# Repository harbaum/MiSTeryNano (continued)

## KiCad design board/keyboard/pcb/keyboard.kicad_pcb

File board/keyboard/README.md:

# MiSTeryNano - Mini ST keyboard

This is a work in progress. It's meant to become a half size keyboard
inspired by the Atari ST series. It's meant to become the basis
of some kind of Mini Atari ST based on the MiSTeryNano FPGA.

They keyboard is primarily designed to be a fully functional design
suited for simple use cases like renaming a file or selecting game
options. It's not meant to be usable to write texts or for any other
productive use case.

## Hardware

The [hardware](pcb) consists of cheap 7x7mm 6 pin momentary switches. These
switches are arranged in the same 15*8 matrix used inside the original
Atari ST keyboard.

The matrix is addressed via serial shift registers requiring four pins
on the controlling device. Two 8-bit serial to parallel shift
registers are used to drive the 15 columnns and a single serial to
parallel shift register is being used to read the eight rows. For
further info on reading the matrix via the serial interface refer
to the [kbd_test Arduino test sketch](kbd_test). The 16th output of
the serial shift registers drive a user conrollable LED in the top right
corner similarily placed to the floppy LED on a Atari STF. This might e.g.
be used in an emulation environment to indicate disk/sd card activity.

The keyboard can either be driven by 3.3V or by 5V and is thus compatible
with nearly all microcontrollers as well as many consumer FPGAs.

## Arduino sketches

The MiSTeryNano keyboard comes with two Arduino sketches. The
[kbd_test](kbd_test) sketch can be installed onto any regular Arduino
Uno, Nano or the Micro and permanently scans the keyboard for pressed
keys and reports the in plain text on the serial monitor. The sketch
also permanently flashes the user led in the top left corner of the
keyboard.  The [arduino_hid](arduino_hid) sketch is meant to be used
in a Sparkfun Pro Micro or Arduino Micro and presents the MiSTeryNano
keyboard as a regular USB keyboard to e.g. a PC or Raspberry Pi. This
sketch uses the user LED to indicate the Caps Lock state and emits F12
for the international key. The later is useful for the US keycaps as
the international key (right of the left shift key) is not present on
US keyboards and can this way be used to open the on-screen-display
or an emulator menu.

## Keycaps

The keycaps have been designed to be printable on a Bambulab Carbon X1
using a 0.4mm nozzle, 0.8mm layer height and two colors of PETG filament.

The keycaps are being designed in FreeCAD using a small macro script
to derive the various variants from a small set of designs. This also
exports [STL files](stl) for printing as well as [WRL files](wrl) for
rendering in kicad.

The image at the top shows they keyboard with US keycaps as currently
designed. The PCB supports the international key right to the left
shift key as well. In the US variant it's covered by the bigger keycap
of the left shift key.

## Assembly

Initially all SMD parts are mounted. The general function can then
be tested with the Arduino test sketch controlling the LED and reacting
to contacts being simulated using tweezers or the like.

Be careful about the orientation when mounting the switches. They will only work correctly in one of the possible two orientations. There are different variants, one e.g. having a bigger opening on the white cover tab or a dot painted on indicating the side to face the keyboards front. It's recommended to test a few switches without soldering them in to verify the correct orientation.

Some optional aligmment spacer grids can be used to help align the
switches during assembly.

All switches and keys are then plugged into these
spacers.

All keypad switches are in place.

The remaining keys are installed and tested row by row.

Finally the keyboard is complete.

A sparkfun Arduino Pro Micro allows the keyboard to
act as a real USB HID keyboard to be used with any PC
or Raspberry Pi or even the FPGA Compantion.

See [this video](https://youtube.com/shorts/clQujxjdr9I) for some
real life typing action.

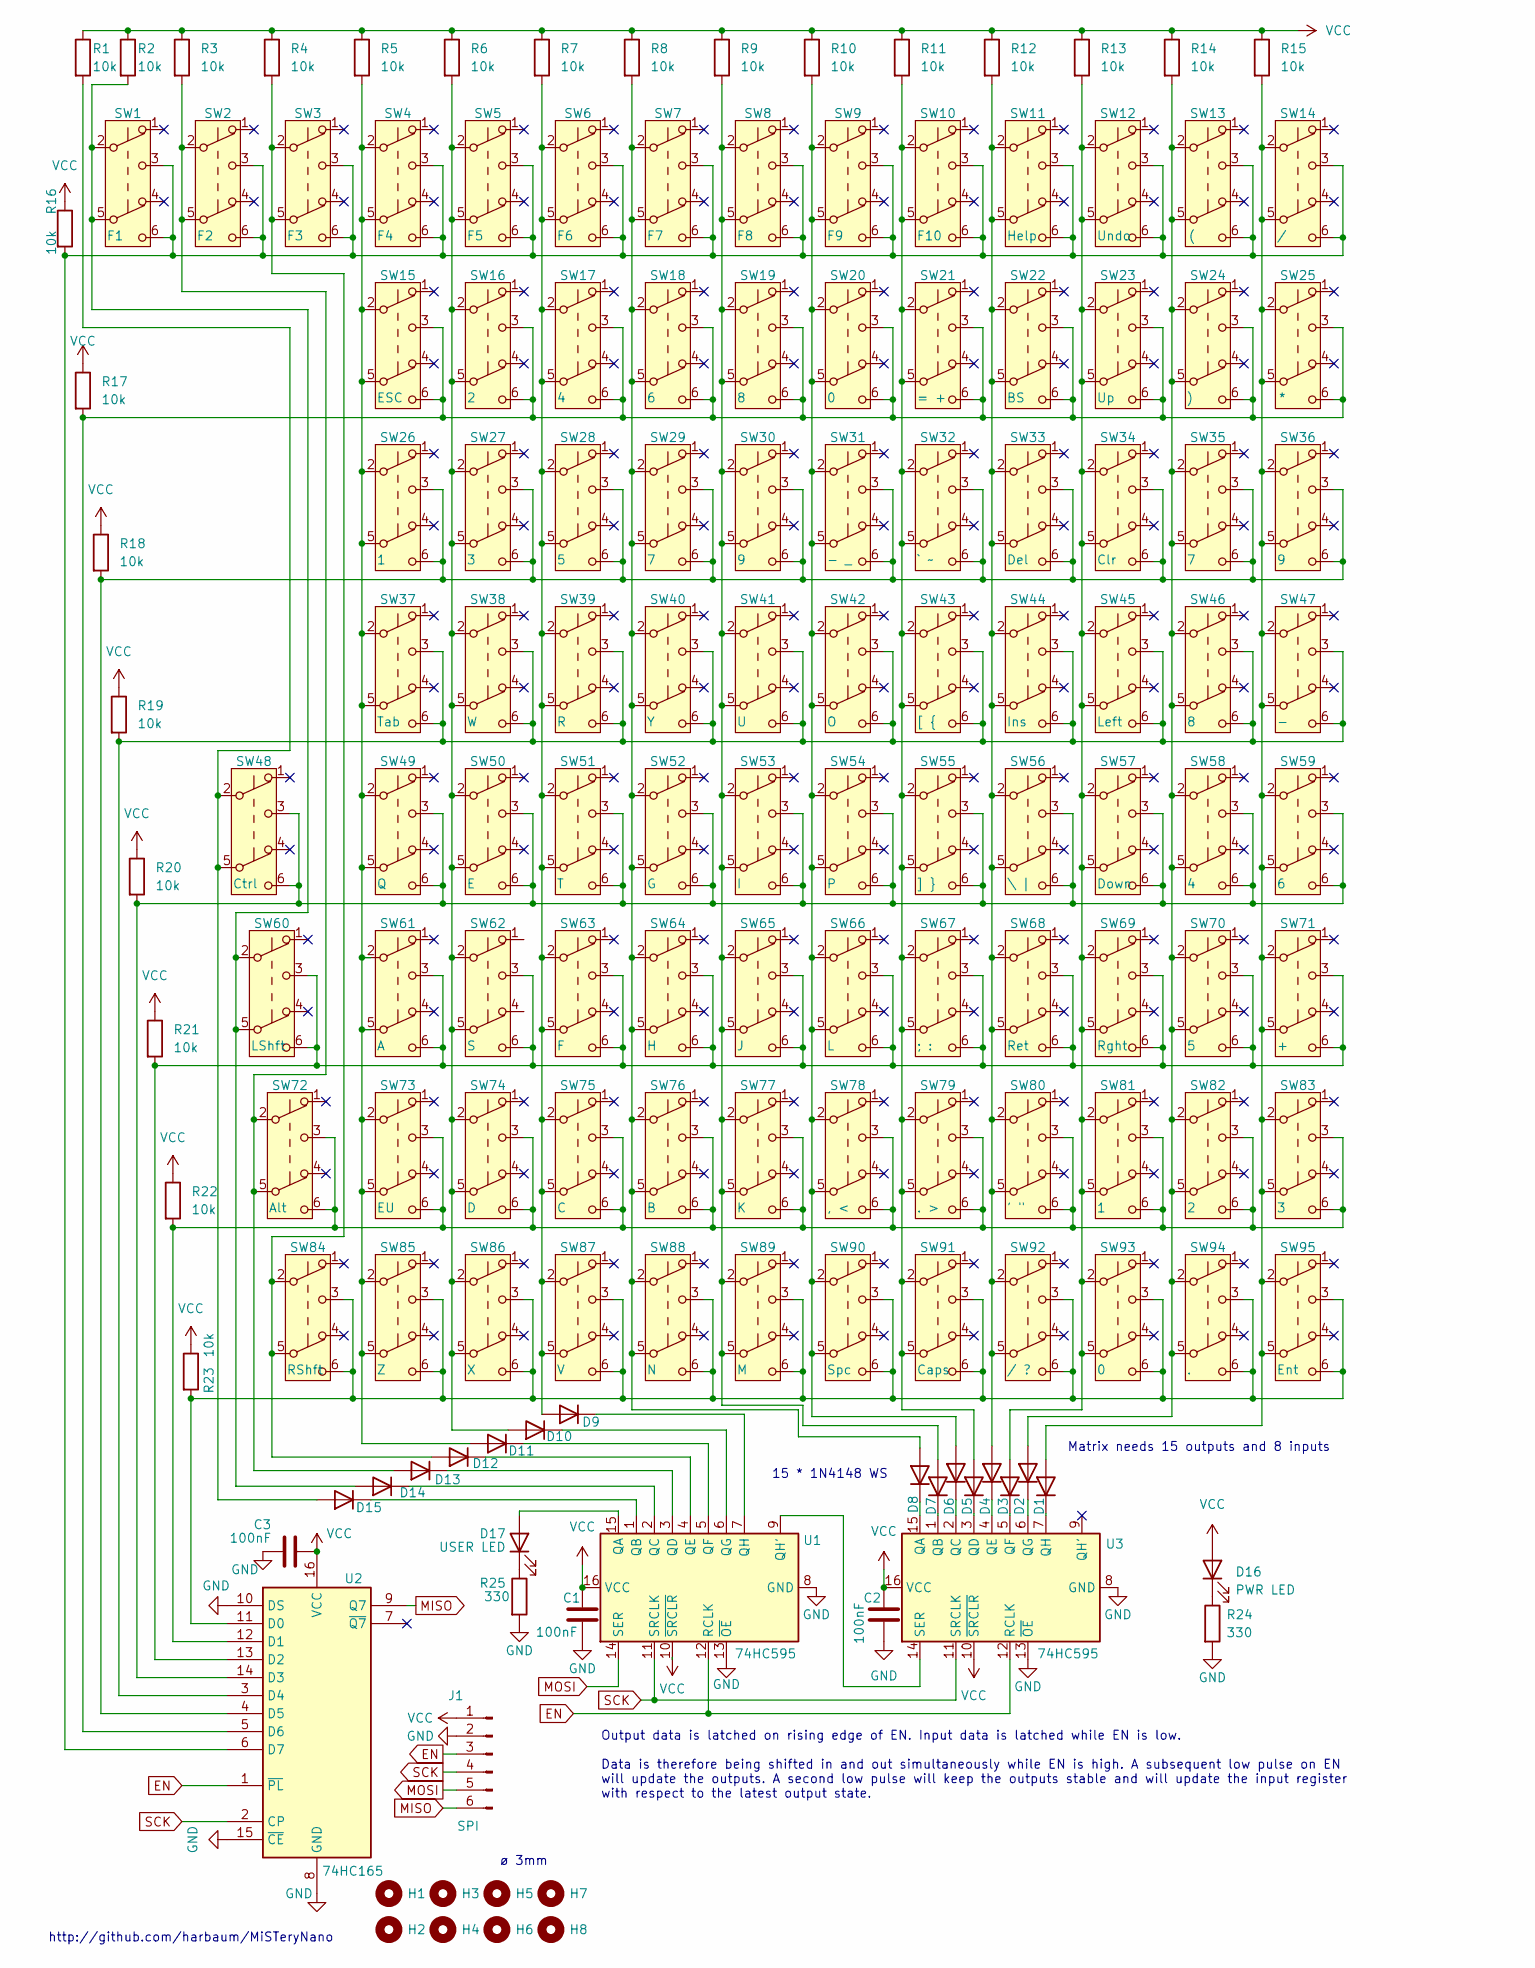
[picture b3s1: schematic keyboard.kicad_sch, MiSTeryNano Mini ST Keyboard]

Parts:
C1, C2, C3: 100nF; C_0805_2012Metric
D1, D2, D3, D4, D5, D6, D7, D8, D9, D10, D11, D12, D13, D14, D15: 1N4148WS; D_SOD-323
D16: PWR LED; LED_0805_2012Metric
D17: USER LED; LED_0805_2012Metric
H1, H2, H3, H4, H5, H6, H7, H8: MountingHole; MountingHole_3mm
J1: SPI; PinHeader_1x06_P2.54mm_Horizontal
R1, R2, R3, R4, R5, R6, R7, R8, R9, R10, R11, R12, R13, R14, R15, R16, R17, R18, R19, R20, R21, R22, R23: 10k; R_0805_2012Metric
R24, R25: 330; R_0805_2012Metric
SW1: F1; sw_7x7_dpdt_6pin
SW2: F2; sw_7x7_dpdt_6pin
SW3: F3; sw_7x7_dpdt_6pin
SW4: F4; sw_7x7_dpdt_6pin
SW5: F5; sw_7x7_dpdt_6pin
SW6: F6; sw_7x7_dpdt_6pin
SW7: F7; sw_7x7_dpdt_6pin
SW8: F8; sw_7x7_dpdt_6pin
SW9: F9; sw_7x7_dpdt_6pin
SW10: F10; sw_7x7_dpdt_6pin
SW11: Help; sw_7x7_dpdt_6pin
SW12: Undo; sw_7x7_dpdt_6pin
SW13: (; sw_7x7_dpdt_6pin
SW14: /; sw_7x7_dpdt_6pin
SW15: ESC; sw_7x7_dpdt_6pin
SW16, SW82: 2; sw_7x7_dpdt_6pin
SW17, SW58: 4; sw_7x7_dpdt_6pin
SW18, SW59: 6; sw_7x7_dpdt_6pin
SW19, SW46: 8; sw_7x7_dpdt_6pin
SW20, SW93: 0; sw_7x7_dpdt_6pin
SW21: = +; sw_7x7_dpdt_6pin
SW22: BS; sw_7x7_dpdt_6pin
SW23: Up; sw_7x7_dpdt_6pin
SW24: ); sw_7x7_dpdt_6pin
SW25: *; sw_7x7_dpdt_6pin
SW26, SW81: 1; sw_7x7_dpdt_6pin
SW27, SW83: 3; sw_7x7_dpdt_6pin
SW28, SW70: 5; sw_7x7_dpdt_6pin
SW29, SW35: 7; sw_7x7_dpdt_6pin
SW30, SW36: 9; sw_7x7_dpdt_6pin
SW31: - _; sw_7x7_dpdt_6pin
SW32: ` ~; sw_7x7_dpdt_6pin
SW33: Del; sw_7x7_dpdt_6pin
SW34: Clr; sw_7x7_dpdt_6pin
SW37: Tab; sw_7x7_dpdt_6pin
SW38: W; sw_7x7_dpdt_6pin
SW39: R; sw_7x7_dpdt_6pin
SW40: Y; sw_7x7_dpdt_6pin
SW41: U; sw_7x7_dpdt_6pin
SW42: O; sw_7x7_dpdt_6pin
SW43: [ {; sw_7x7_dpdt_6pin
SW44: Ins; sw_7x7_dpdt_6pin
SW45: Left; sw_7x7_dpdt_6pin
SW47: -; sw_7x7_dpdt_6pin
SW48: Ctrl; sw_7x7_dpdt_6pin
SW49: Q; sw_7x7_dpdt_6pin
SW50: E; sw_7x7_dpdt_6pin
SW51: T; sw_7x7_dpdt_6pin
SW52: G; sw_7x7_dpdt_6pin
SW53: I; sw_7x7_dpdt_6pin
SW54: P; sw_7x7_dpdt_6pin
SW55: ] }; sw_7x7_dpdt_6pin
SW56: \ |; sw_7x7_dpdt_6pin
SW57: Down; sw_7x7_dpdt_6pin
SW60: LShft; sw_7x7_dpdt_6pin
SW61: A; sw_7x7_dpdt_6pin
SW62: S; sw_7x7_dpdt_6pin
SW63: F; sw_7x7_dpdt_6pin
SW64: H; sw_7x7_dpdt_6pin
SW65: J; sw_7x7_dpdt_6pin
SW66: L; sw_7x7_dpdt_6pin
SW67: ; :; sw_7x7_dpdt_6pin
SW68: Ret; sw_7x7_dpdt_6pin
SW69: Rght; sw_7x7_dpdt_6pin
SW71: +; sw_7x7_dpdt_6pin
SW72: Alt; sw_7x7_dpdt_6pin
SW73: EU; sw_7x7_dpdt_6pin
SW74: D; sw_7x7_dpdt_6pin
SW75: C; sw_7x7_dpdt_6pin
SW76: B; sw_7x7_dpdt_6pin
SW77: K; sw_7x7_dpdt_6pin
SW78: , <; sw_7x7_dpdt_6pin
SW79: . >; sw_7x7_dpdt_6pin
SW80: ' "; sw_7x7_dpdt_6pin
SW84: RShft; sw_7x7_dpdt_6pin
SW85: Z; sw_7x7_dpdt_6pin
SW86: X; sw_7x7_dpdt_6pin
SW87: V; sw_7x7_dpdt_6pin
SW88: N; sw_7x7_dpdt_6pin
SW89: M; sw_7x7_dpdt_6pin
SW90: Spc; sw_7x7_dpdt_6pin
SW91: Caps; sw_7x7_dpdt_6pin
SW92: / ?; sw_7x7_dpdt_6pin
SW94: .; sw_7x7_dpdt_6pin
SW95: Ent; sw_7x7_dpdt_6pin
U1, U3: 74HC595; SOIC-16_3.9x9.9mm_P1.27mm
U2: 74HC165; SO-16_3.9x9.9mm_P1.27mm

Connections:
EN: J1.3, U1.12 (RCLK), U2.1 (~PL), U3.12 (RCLK)
GND: C1.2, C2.2, C3.1, J1.2, R24.2, R25.2, U1.8 (GND), U1.13 (~OE), U2.8 (GND), U2.10 (DS), U2.15 (~CE), U3.8 (GND), U3.13 (~OE)
MISO: J1.6, U2.9 (Q7)
MOSI: J1.5, U1.14 (SER)
unnamed: D1.2 (A), R15.2, SW14.2 (B), SW14.5 (B), SW25.2 (B), SW25.5 (B), SW36.2 (B), SW36.5 (B), SW47.2 (B), SW47.5 (B), SW59.2 (B), SW59.5 (B), SW71.2 (B), SW71.5 (B), SW83.2 (B), SW83.5 (B), SW95.2 (B), SW95.5 (B)
unnamed: D1.1 (K), U3.7 (QH)
unnamed: D2.2 (A), R14.2, SW13.2 (B), SW13.5 (B), SW24.2 (B), SW24.5 (B), SW35.2 (B), SW35.5 (B), SW46.2 (B), SW46.5 (B), SW58.2 (B), SW58.5 (B), SW70.2 (B), SW70.5 (B), SW82.2 (B), SW82.5 (B), SW94.2 (B), SW94.5 (B)
unnamed: D2.1 (K), U3.6 (QG)
unnamed: D3.2 (A), R13.2, SW12.2 (B), SW12.5 (B), SW23.2 (B), SW23.5 (B), SW34.2 (B), SW34.5 (B), SW45.2 (B), SW45.5 (B), SW57.2 (B), SW57.5 (B), SW69.2 (B), SW69.5 (B), SW81.2 (B), SW81.5 (B), SW93.2 (B), SW93.5 (B)
unnamed: D3.1 (K), U3.5 (QF)
unnamed: D4.2 (A), R12.2, SW11.2 (B), SW11.5 (B), SW22.2 (B), SW22.5 (B), SW33.2 (B), SW33.5 (B), SW44.2 (B), SW44.5 (B), SW56.2 (B), SW56.5 (B), SW68.2 (B), SW68.5 (B), SW80.2 (B), SW80.5 (B), SW92.2 (B), SW92.5 (B)
unnamed: D4.1 (K), U3.4 (QE)
unnamed: D5.2 (A), R11.2, SW10.2 (B), SW10.5 (B), SW21.2 (B), SW21.5 (B), SW32.2 (B), SW32.5 (B), SW43.2 (B), SW43.5 (B), SW55.2 (B), SW55.5 (B), SW67.2 (B), SW67.5 (B), SW79.2 (B), SW79.5 (B), SW91.2 (B), SW91.5 (B)
unnamed: D5.1 (K), U3.3 (QD)
unnamed: D6.2 (A), R10.2, SW9.2 (B), SW9.5 (B), SW20.2 (B), SW20.5 (B), SW31.2 (B), SW31.5 (B), SW42.2 (B), SW42.5 (B), SW54.2 (B), SW54.5 (B), SW66.2 (B), SW66.5 (B), SW78.2 (B), SW78.5 (B), SW90.2 (B), SW90.5 (B)
unnamed: D6.1 (K), U3.2 (QC)
unnamed: D7.2 (A), R9.2, SW8.2 (B), SW8.5 (B), SW19.2 (B), SW19.5 (B), SW30.2 (B), SW30.5 (B), SW41.2 (B), SW41.5 (B), SW53.2 (B), SW53.5 (B), SW65.2 (B), SW65.5 (B), SW77.2 (B), SW77.5 (B), SW89.2 (B), SW89.5 (B)
unnamed: D7.1 (K), U3.1 (QB)
unnamed: D8.2 (A), R8.2, SW7.2 (B), SW7.5 (B), SW18.2 (B), SW18.5 (B), SW29.2 (B), SW29.5 (B), SW40.2 (B), SW40.5 (B), SW52.2 (B), SW52.5 (B), SW64.2 (B), SW64.5 (B), SW76.2 (B), SW76.5 (B), SW88.2 (B), SW88.5 (B)
unnamed: D8.1 (K), U3.15 (QA)
unnamed: D9.2 (A), R7.2, SW6.2 (B), SW6.5 (B), SW17.2 (B), SW17.5 (B), SW28.2 (B), SW28.5 (B), SW39.2 (B), SW39.5 (B), SW51.2 (B), SW51.5 (B), SW63.2 (B), SW63.5 (B), SW75.2 (B), SW75.5 (B), SW87.2 (B), SW87.5 (B)
unnamed: D9.1 (K), U1.7 (QH)
unnamed: D10.2 (A), R6.2, SW5.2 (B), SW5.5 (B), SW16.2 (B), SW16.5 (B), SW27.2 (B), SW27.5 (B), SW38.2 (B), SW38.5 (B), SW50.2 (B), SW50.5 (B), SW62.2 (B), SW62.5 (B), SW74.2 (B), SW74.5 (B), SW86.2 (B), SW86.5 (B)
unnamed: D10.1 (K), U1.6 (QG)
unnamed: D11.2 (A), R5.2, SW4.2 (B), SW4.5 (B), SW15.2 (B), SW15.5 (B), SW26.2 (B), SW26.5 (B), SW37.2 (B), SW37.5 (B), SW49.2 (B), SW49.5 (B), SW61.2 (B), SW61.5 (B), SW73.2 (B), SW73.5 (B), SW85.2 (B), SW85.5 (B)
unnamed: D11.1 (K), U1.5 (QF)
unnamed: D12.2 (A), R4.2, SW3.2 (B), SW3.5 (B), SW84.2 (B), SW84.5 (B)
unnamed: D12.1 (K), U1.4 (QE)
unnamed: D13.2 (A), R3.2, SW2.2 (B), SW2.5 (B), SW72.2 (B), SW72.5 (B)
unnamed: D13.1 (K), U1.3 (QD)
unnamed: D14.2 (A), R2.2, SW1.2 (B), SW1.5 (B), SW60.2 (B), SW60.5 (B)
unnamed: D14.1 (K), U1.2 (QC)
unnamed: D15.2 (A), R1.2, SW48.2 (B), SW48.5 (B)
unnamed: D15.1 (K), U1.1 (QB)
unnamed: D16.1 (K), R24.1
unnamed: D17.2 (A), U1.15 (QA)
unnamed: D17.1 (K), R25.1
unnamed: U1.9 (QH'), U3.14 (SER)
unnamed: R23.2, SW84.3 (C), SW84.6 (C), SW85.3 (C), SW85.6 (C), SW86.3 (C), SW86.6 (C), SW87.3 (C), SW87.6 (C), SW88.3 (C), SW88.6 (C), SW89.3 (C), SW89.6 (C), SW90.3 (C), SW90.6 (C), SW91.3 (C), SW91.6 (C), SW92.3 (C), SW92.6 (C), SW93.3 (C), SW93.6 (C), SW94.3 (C), SW94.6 (C), SW95.3 (C), SW95.6 (C), U2.11 (D0)
unnamed: R22.2, SW72.3 (C), SW72.6 (C), SW73.3 (C), SW73.6 (C), SW74.3 (C), SW74.6 (C), SW75.3 (C), SW75.6 (C), SW76.3 (C), SW76.6 (C), SW77.3 (C), SW77.6 (C), SW78.3 (C), SW78.6 (C), SW79.3 (C), SW79.6 (C), SW80.3 (C), SW80.6 (C), SW81.3 (C), SW81.6 (C), SW82.3 (C), SW82.6 (C), SW83.3 (C), SW83.6 (C), U2.12 (D1)
unnamed: R21.2, SW60.3 (C), SW60.6 (C), SW61.3 (C), SW61.6 (C), SW62.3 (C), SW62.6 (C), SW63.3 (C), SW63.6 (C), SW64.3 (C), SW64.6 (C), SW65.3 (C), SW65.6 (C), SW66.3 (C), SW66.6 (C), SW67.3 (C), SW67.6 (C), SW68.3 (C), SW68.6 (C), SW69.3 (C), SW69.6 (C), SW70.3 (C), SW70.6 (C), SW71.3 (C), SW71.6 (C), U2.13 (D2)
unnamed: R20.2, SW48.3 (C), SW48.6 (C), SW49.3 (C), SW49.6 (C), SW50.3 (C), SW50.6 (C), SW51.3 (C), SW51.6 (C), SW52.3 (C), SW52.6 (C), SW53.3 (C), SW53.6 (C), SW54.3 (C), SW54.6 (C), SW55.3 (C), SW55.6 (C), SW56.3 (C), SW56.6 (C), SW57.3 (C), SW57.6 (C), SW58.3 (C), SW58.6 (C), SW59.3 (C), SW59.6 (C), U2.14 (D3)
unnamed: R19.2, SW37.3 (C), SW37.6 (C), SW38.3 (C), SW38.6 (C), SW39.3 (C), SW39.6 (C), SW40.3 (C), SW40.6 (C), SW41.3 (C), SW41.6 (C), SW42.3 (C), SW42.6 (C), SW43.3 (C), SW43.6 (C), SW44.3 (C), SW44.6 (C), SW45.3 (C), SW45.6 (C), SW46.3 (C), SW46.6 (C), SW47.3 (C), SW47.6 (C), U2.3 (D4)
unnamed: R18.2, SW26.3 (C), SW26.6 (C), SW27.3 (C), SW27.6 (C), SW28.3 (C), SW28.6 (C), SW29.3 (C), SW29.6 (C), SW30.3 (C), SW30.6 (C), SW31.3 (C), SW31.6 (C), SW32.3 (C), SW32.6 (C), SW33.3 (C), SW33.6 (C), SW34.3 (C), SW34.6 (C), SW35.3 (C), SW35.6 (C), SW36.3 (C), SW36.6 (C), U2.4 (D5)
unnamed: R17.2, SW15.3 (C), SW15.6 (C), SW16.3 (C), SW16.6 (C), SW17.3 (C), SW17.6 (C), SW18.3 (C), SW18.6 (C), SW19.3 (C), SW19.6 (C), SW20.3 (C), SW20.6 (C), SW21.3 (C), SW21.6 (C), SW22.3 (C), SW22.6 (C), SW23.3 (C), SW23.6 (C), SW24.3 (C), SW24.6 (C), SW25.3 (C), SW25.6 (C), U2.5 (D6)
unnamed: R16.2, SW1.3 (C), SW1.6 (C), SW2.3 (C), SW2.6 (C), SW3.3 (C), SW3.6 (C), SW4.3 (C), SW4.6 (C), SW5.3 (C), SW5.6 (C), SW6.3 (C), SW6.6 (C), SW7.3 (C), SW7.6 (C), SW8.3 (C), SW8.6 (C), SW9.3 (C), SW9.6 (C), SW10.3 (C), SW10.6 (C), SW11.3 (C), SW11.6 (C), SW12.3 (C), SW12.6 (C), SW13.3 (C), SW13.6 (C), SW14.3 (C), SW14.6 (C), U2.6 (D7)
SCK: J1.4, U1.11 (SRCLK), U2.2 (CP), U3.11 (SRCLK)
VCC: C1.1, C2.1, C3.2, D16.2 (A), J1.1, R1.1, R2.1, R3.1, R4.1, R5.1, R6.1, R7.1, R8.1, R9.1, R10.1, R11.1, R12.1, R13.1, R14.1, R15.1, R16.1, R17.1, R18.1, R19.1, R20.1, R21.1, R22.1, R23.1, U1.10 (~SRCLR), U1.16 (VCC), U2.16 (VCC), U3.10 (~SRCLR), U3.16 (VCC)

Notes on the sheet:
Matrix needs 15 outputs and 8 inputs
ø 3mm
http://github.com/harbaum/MiSTeryNano
15 * 1N4148 WS
Output data is latched on rising edge of EN. Input data is latched while EN is low. Data is therefore being shifted in and out simultaneously while EN is high. A subsequent low pulse on EN will update the outputs. A second low pulse will keep the outputs stable and will update the input register wi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

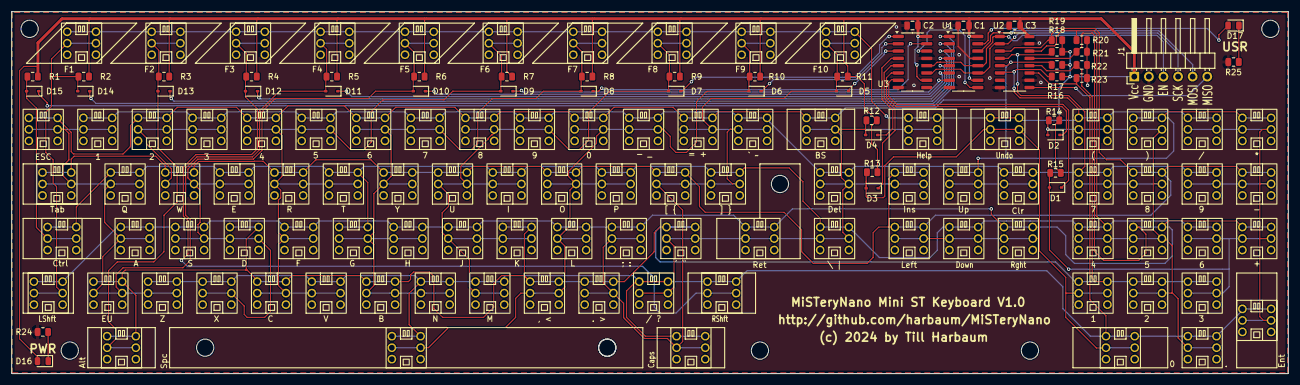
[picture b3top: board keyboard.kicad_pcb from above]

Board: 2 copper layers, 222.2 x 63.0 mm, 153 parts (0 on the bottom side), 48 nets.

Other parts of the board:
H8#2: MountingHole; MountingHole_3mm

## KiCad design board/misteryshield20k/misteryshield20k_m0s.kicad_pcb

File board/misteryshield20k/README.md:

# MiSTeryNano MIDI shield for Tang Nano 20k

This is a base board for the Tang Nano 20K and optionally the M0S Dock.
It features:

  * Headers to plug the Tang Nano 20K
  * A seperate USB power supply (old variant only)
    * Used if the Tang Nano 20K is being used as a USB host itself
    * Can be broken off to make room for a M0S Dock
  * M0S Dock connector
  * Atari style joystick
    * Supports two buttons
    * Including 5V supply and 5V level shifters
    * Works with DB9 joystcks and mice
  * MIDI
    * MIDI OUT with driver chip to protect Tang Nano 20K
    * MIDI IN with optocoupler to protect Tang Nano 20K

PCBA production files for JLCPCB are availble [here](jlcpcb).

## Variants

There are now two variants of the board:

  * The original variant including a small PCB breakout with a USB-C
  connector. This variant could theoretically be used without M0S
  Dock. But in fact the M0S Dock is currently needed by many cores and
  the USB-C part needs to be cut off to make space for the M0S
  Dock. However, it turned out that some people damage the PCB in the
  process of cutting this part off. That's why the second M0S variant
  now exists.
  
  * The M0S variant does not include the USB-C part and can only be
  used in conjunction with a M0S Dock. This is the preferred version
  as nothing has to be cut to use it. However, this variant has not
  been tested, yet. No problems are expected, but please report back
  if you successfully order and use one of these.

The part carrying the USB connector can be cut away making room for a
M0S Dock which will then also be used to provide power to the Tang
Nano 20K.

[PDF](misteryshield20k.pdf)

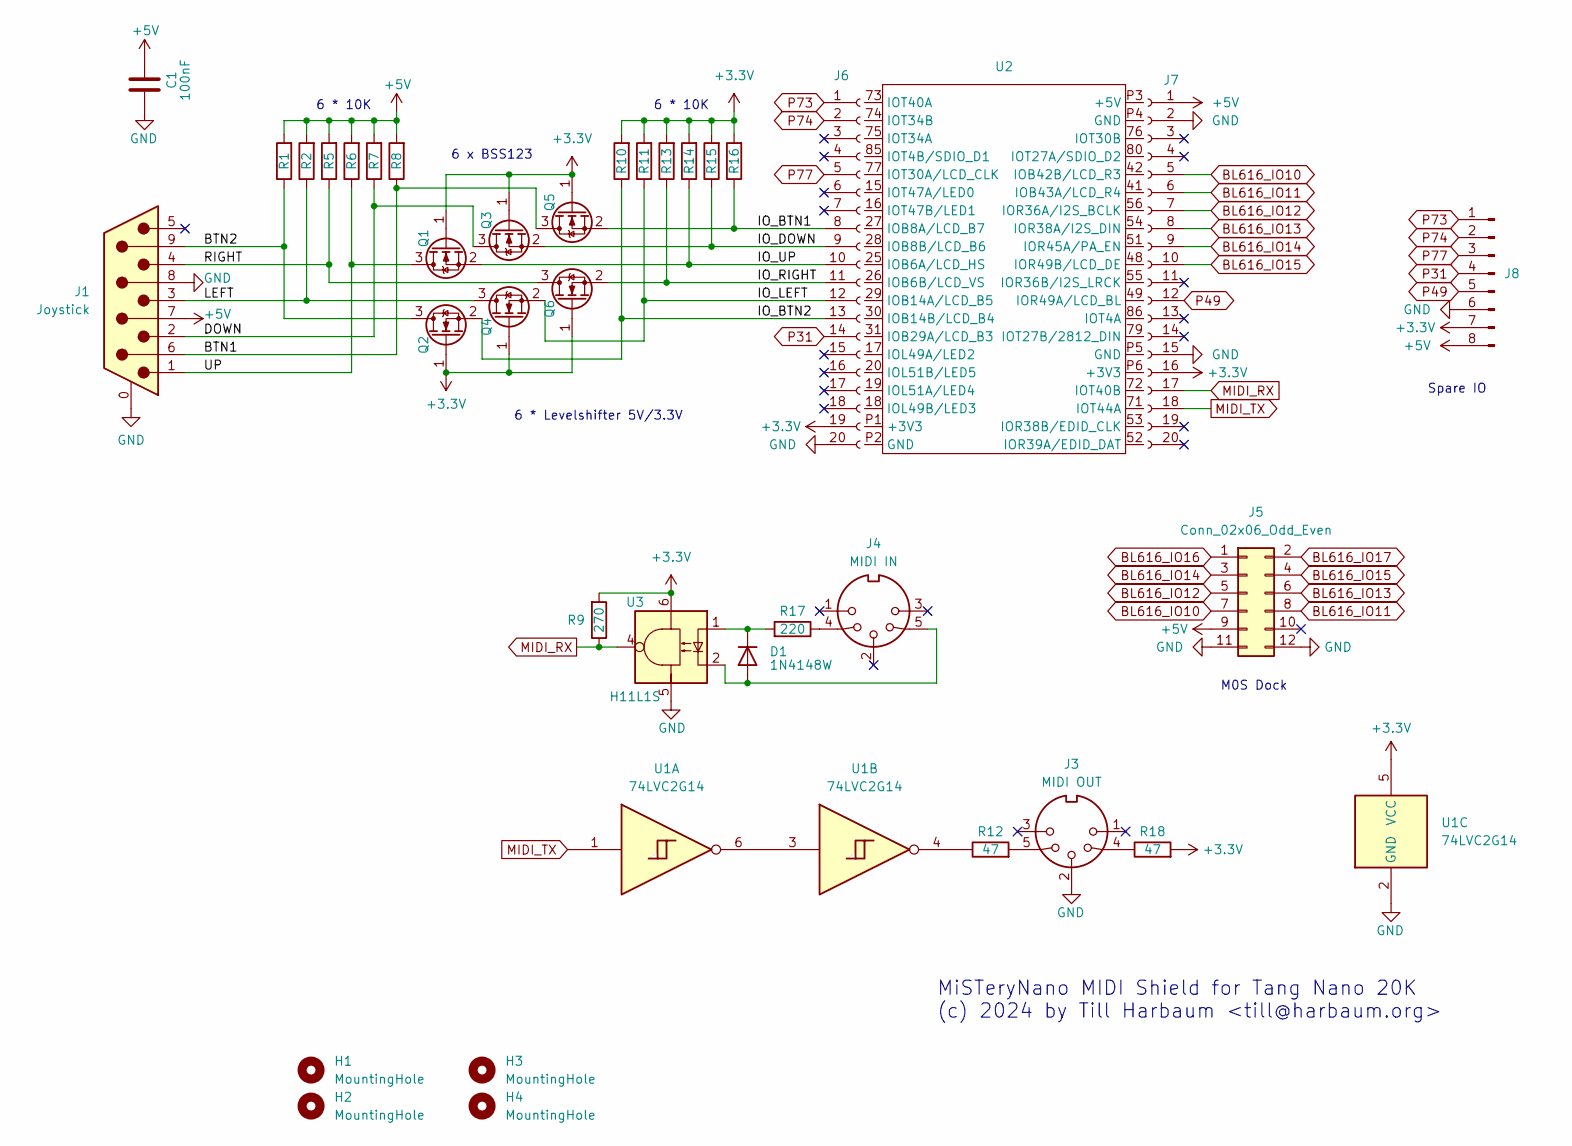
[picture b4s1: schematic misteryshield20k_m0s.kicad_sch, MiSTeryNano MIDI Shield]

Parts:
C1: 100nF; C_0805_2012Metric; LCSC Part # C49678
D1: 1N4148W; D_SOD-123; LCSC Part # C81598
H1, H2, H3, H4: MountingHole; MountingHole_3.2mm_M3
J1: Joystick; DSUB-9_Male_Horizontal_P2.77x2.84mm_EdgePinOffset7.70mm_Hou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; LCSC Part # C141880
J3: MIDI OUT; din-5; LCSC Part # C2939346
J4: MIDI IN; din-5; LCSC Part # C2939346
J5: Conn_02x06_Odd_Even; PinSocket_2x06_P2.54mm_Horizontal; LCSC Part # C5333437
J6, J7: Conn_01x20_Socket; PinSocket_1x20_P2.54mm_Vertical; LCSC Part # C5224030
J8: Conn_02x04_Pin; PinHeader_2x04_P2.54mm_Vertical; LCSC Part # C706894
Q1, Q2, Q3, Q4, Q5, Q6: BSS123; SOT-23; JLCPCB Rotation Offset 180
R1, R2, R5, R6, R7, R8, R10, R11, R13, R14, R15, R16: 10k; R_0805_2012Metric; LCSC Part # C17414
R9: 270; R_0805_2012Metric; LCSC Part # C17590
R12, R18: 47; R_0805_2012Metric; LCSC Part # C17714
R17: 220; R_0805_2012Metric; LCSC Part # C17557
U1: 74LVC2G14; SOT-23-6; LCSC Part # C5375976
U2: tang nano 20k
U3: H11L1S; SMDIP-6_W9.53mm; LCSC Part # C78589

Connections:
+3.3V: J6.19, J7.16, J8.7, Q1.1 (G), Q2.1 (G), Q3.1 (G), Q4.1 (G), Q5.1 (G), Q6.1 (G), R9.2, R10.2, R11.2, R13.2, R14.2, R15.2, R16.2, R18.2, U1.5 (VCC), U3.6
+5V: C1.2, J1.7, J5.9, J7.1, J8.8, R1.2, R2.2, R5.2, R6.2, R7.2, R8.2
/BTN1: J1.6, Q5.3 (D), R8.1
/BTN2: J1.9, Q2.3 (D), R1.1
/DOWN: J1.2, Q3.3 (D), R7.1
/IO_BTN1: J6.8, Q5.2 (S), R16.1
/IO_BTN2: J6.13, Q2.2 (S), R10.1
/IO_DOWN: J6.9, Q3.2 (S), R15.1
/IO_LEFT: J6.12, Q4.2 (S), R11.1
/IO_RIGHT: J6.11, Q6.2 (S), R13.1
/IO_UP: J6.10, Q1.2 (S), R14.1
/LEFT: J1.3, Q4.3 (D), R2.1
/RIGHT: J1.4, Q6.3 (D), R5.1
/UP: J1.1, Q1.3 (D), R6.1
BL616_IO10: J5.7, J7.5
BL616_IO11: J5.8, J7.6
BL616_IO12: J5.5, J7.7
BL616_IO13: J5.6, J7.8
BL616_IO14: J5.3, J7.9
BL616_IO15: J5.4, J7.10
BL616_IO16: J5.1
BL616_IO17: J5.2
GND: C1.1, J1.0 (PAD), J1.8, J3.2, J5.11, J5.12, J6.20, J7.2, J7.15, J8.6, U1.2 (GND), U3.5
MIDI_RX: J7.17, R9.1, U3.4
MIDI_TX: J7.18, U1.1
unnamed: D1.2 (A), J4.5, U3.2
unnamed: D1.1 (K), R17.2, U3.1
unnamed: J3.4, R18.1
unnamed: J3.5, R12.2
unnamed: J4.4, R17.1
unnamed: R12.1, U1.4
unnamed: U1.3, U1.6
P31: J6.14, J8.4
P49: J7.12, J8.5
P73: J6.1, J8.1
P74: J6.2, J8.2
P77: J6.5, J8.3

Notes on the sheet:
6 * Levelshifter 5V/3.3V
Spare IO
MiSTeryNano MIDI Shield for Tang Nano 20K (c) 2024 by Till Harbaum <till@harbaum.org>
6 * 10K
6 x BSS123
M0S Dock

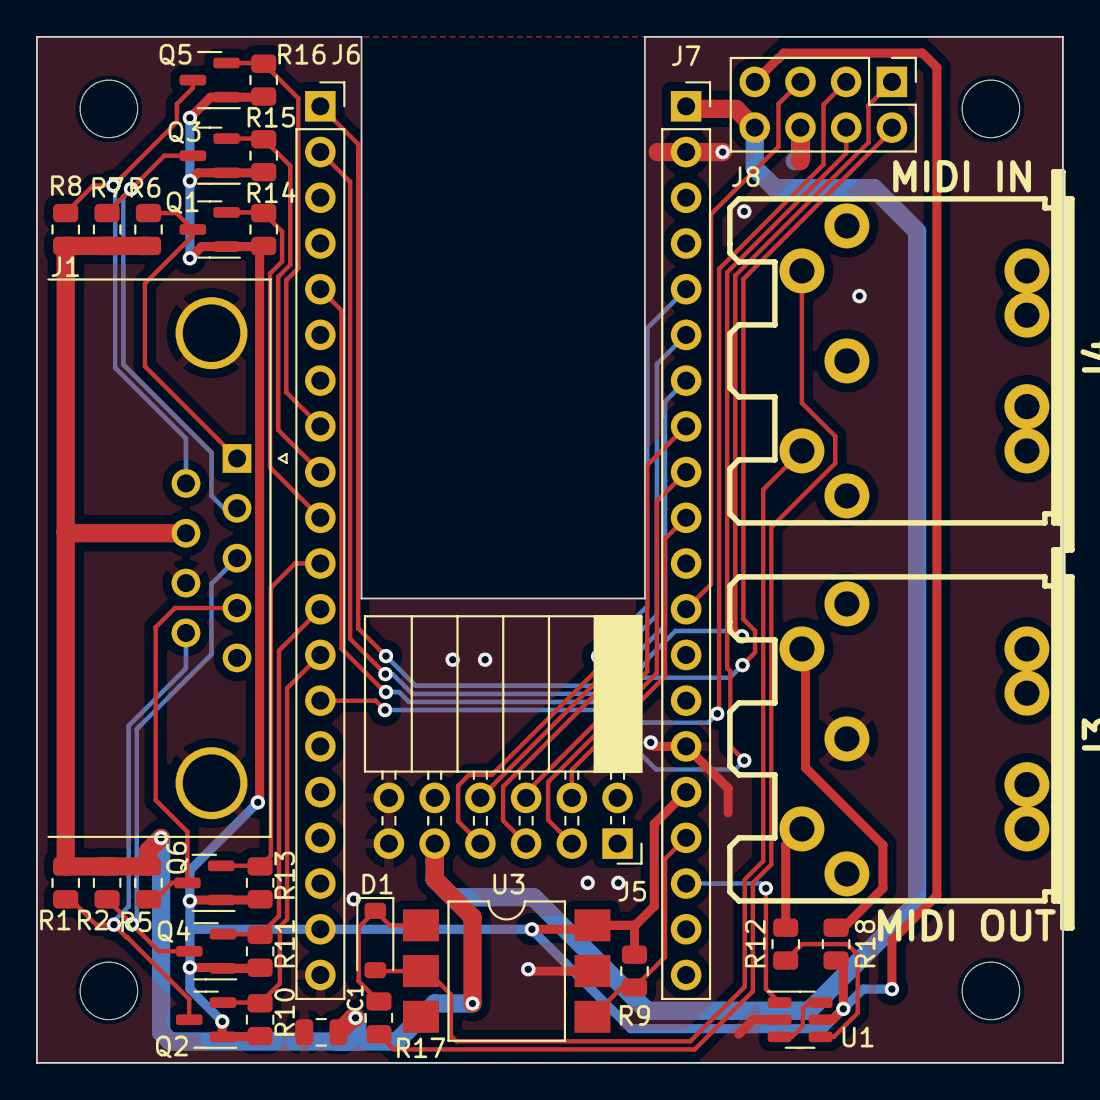
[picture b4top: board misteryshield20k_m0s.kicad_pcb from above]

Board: 2 copper layers, 57.0 x 57.0 mm, 37 parts (0 on the bottom side), 35 nets.

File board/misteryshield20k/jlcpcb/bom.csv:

Designator,Footprint,Quantity,Value,LCSC Part #
C1,0805,1,100nF, C49678
D1,D_SOD-123,1,1N4148W,C81598
J1,DSUB-9_Male_Horizontal_P2.77x2.84mm_EdgePinOffset7.70mm_Housed_MountingHolesOffset9.12mm,1,Joystick,C141880
J2,TYPE-C-31-M-12,1,USB_C_Receptacle_USB2.0,C2927037
J3,din-5,1,MIDI OUT,C2939346
J4,din-5,1,MIDI IN,C2939346
J5,PinSocket_2x06_P2.54mm_Horizontal,1,Conn_02x06_Odd_Even,C5333437
"J6, J7",PinSocket_1x20_P2.54mm_Vertical,2,Conn_01x20_Socket, C5224030
J8,PinHeader_2x04_P2.54mm_Vertical,1,Conn_02x04_Pin, C706894
"Q1, Q2, Q3, Q4, Q5, Q6",SOT-23,6,BSS123,C79015
R1,0805,1,10k,C17414
R10,0805,1,10k,C17414
R11,0805,1,10k,C17414
R12,0805,1,47, C17714
R13,0805,1,10k,C17414
R14,0805,1,10k,C17414
R15,0805,1,10k,C17414
R16,0805,1,10k,C17414
R17,0805,1,220, C17557
R18,0805,1,47, C17714
R2,0805,1,10k,C17414
R3,0805,1,5k1,C27834
R4,0805,1,5k1,C27834
R5,0805,1,10k,C17414
R6,0805,1,10k,C17414
R7,0805,1,10k,C17414
R8,0805,1,10k,C17414
R9,0805,1,270, C17590
U1,SOT-23-6,1,74LVC2G14,C5375976
U3,SMDIP-6_W9.53mm,1,H11L1S,C78589

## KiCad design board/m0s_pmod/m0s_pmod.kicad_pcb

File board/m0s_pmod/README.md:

# M0S PMOD

The M0S PMOD adapter connects a  [M0S Dock](https://wiki.sipeed.com/hardware/en/maixzero/m0s/m0s.html) to any FPGA board with PMOD ports.

The M0S PMOD can e.g. be used with the [Tang Primer
25K](https://wiki.sipeed.com/hardware/en/tang/tang-primer-25k/primer-25k.html) or
the [Tang Mega 138K](https://wiki.sipeed.com/hardware/en/tang/tang-mega-138k/mega-138k-pro.html). This
may e.g. be used to run the MiSTeryNano firmware on the M0S Dock and
to give the MiSTeryNano core running on the Tang Primer 25K advanced
USB host capabilites, the On-Screen-Display and all file system
handling needed.

The device is rather simple and mainly consists of a 3.3V to 5V boost
converter prividing 5V to the M0S Doch from the 3.3V available on the
PMOD connector. While the M0S itself runs on 3.3V, the 5V are needed
for the M0S Dock to provide powre to the USB port when acting as a USB
host. The LED is powered from the 3.3V returned by the M0S Dock and
will indicate that the M0S Dock is properly powered.

[PDF](m0s_pmod_schematic.pdf)

## Production data

Complete production data for the JLCPCB PCBA service is [included](jlcpcb).

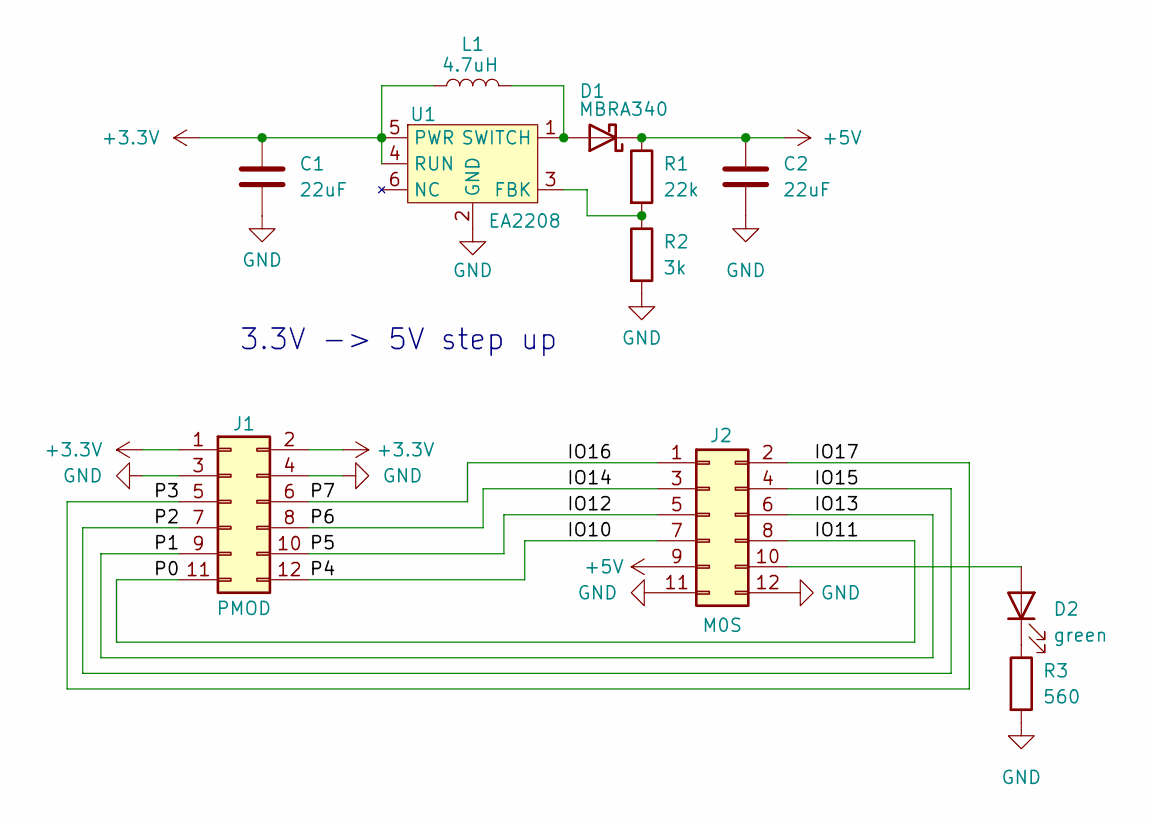
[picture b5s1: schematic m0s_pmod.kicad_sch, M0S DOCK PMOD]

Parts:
C1, C2: 22uF; C_1206_3216Metric
D1: MBRA340; D_SMA; LCSC Part # C5140034
D2: green; LED_0805_2012Metric
J1: PMOD; PinHeader_2x06_P2.54mm_Horizontal; JLCPCB Position Offset -6.35,-1.5
J2: M0S; PinSocket_2x06_P2.54mm_Horizontal; JLCPCB Position Offset 6.35,-1.5
L1: 4.7uH; L_6.3x6.3_H3; LCSC Part # C108287
R1: 22k; R_0805_2012Metric
R2: 3k; R_0805_2012Metric
R3: 560; R_0805_2012Metric
U1: EA2208; SOT-23-6; JLCPCB Rotation Offset 180

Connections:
+3.3V: C1.1, J1.1, J1.2, L1.1, U1.4 (RUN), U1.5 (PWR)
+5V: C2.1, D1.1 (K), J2.9, R1.1
/IO10: J1.12, J2.7
/IO11: J1.11, J2.8
/IO12: J1.10, J2.5
/IO13: J1.9, J2.6
/IO14: J1.8, J2.3
/IO15: J1.7, J2.4
/IO16: J1.6, J2.1
/IO17: J1.5, J2.2
GND: C1.2, C2.2, J1.3, J1.4, J2.11, J2.12, R2.2, R3.2, U1.2 (GND)
unnamed: D1.2 (A), L1.2, U1.1 (SWITCH)
unnamed: D2.2 (A), J2.10
unnamed: D2.1 (K), R3.1
unnamed: R1.2, R2.1, U1.3 (FBK)

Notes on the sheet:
3.3V -> 5V step up

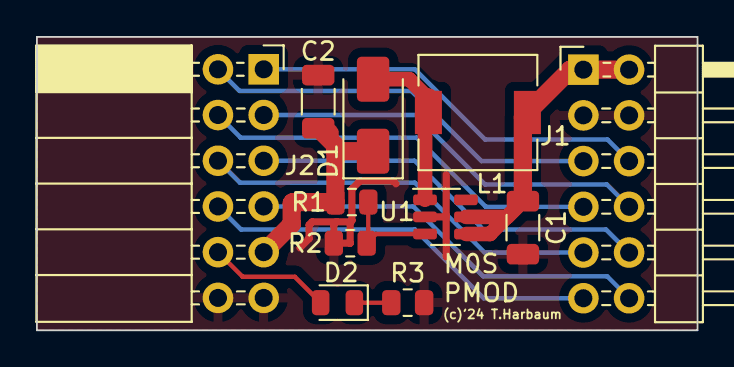
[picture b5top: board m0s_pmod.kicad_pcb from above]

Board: 2 copper layers, 36.7 x 16.3 mm, 11 parts (0 on the bottom side), 15 nets.

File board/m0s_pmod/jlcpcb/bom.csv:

Designator,Footprint,Quantity,Value,LCSC Part #
C1,1206,1,22uF,
C2,1206,1,22uF,
D1,D_SMA,1,MBRA340, C5140034
D2,0805,1,green,
J1,PinHeader_2x06_P2.54mm_Horizontal,1,PMOD,C2911299
J2,PinSocket_2x06_P2.54mm_Horizontal,1,M0S,C5333437
L1,L_6.3x6.3_H3,1,4.7uH,C108287
R1,0805,1,22k,
R2,0805,1,3k,
R3,0805,1,560,
U1,SOT-23-6,1,EA2208,

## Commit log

2023-09-25 Initial readme
2023-09-25 Add missing features
2023-09-26 Initial realease
2023-09-26 Mouse connection documented
2023-09-26 Add floppy disk simulation
2023-09-27 Add flash testbench
2023-09-27 Add ram testbench
2023-09-27 Fix image path
2023-09-27 Links to related projects
2023-09-30 SD FAT support and various improvements
2023-09-30 Update missing change
2023-10-01 Add more tests
2023-10-01 Link to releases
2023-10-02 Cleanup
2023-10-02 Wiring diagram
2023-10-02 Update wiring image
2023-10-02 Update wiring
2023-10-04 Support for monochrome video and external config pins
2023-10-04 Configuration of STE mode
2023-10-12 Add on-screen-display for floppy image selection
2023-10-12 Update wire schema
2023-10-13 Add menu button to image
2023-10-13 Add trackball image
2023-10-13 resize image
2023-10-13 Start BL616 documentation
2023-10-14 Disk a link
2023-10-14 Allow other file after file not found
2023-10-19 First version of M0S Dock USB HID to PS2
2023-10-19 hid usb descriptions
2023-10-19 More explanations
2023-10-20 Update bl616 doc
2023-10-20 Fix keyboard handling
2023-10-24 Option to compile for on-board MCU
2023-10-24 PS/2 wiring
2023-10-24 Fix PS2 wiring
2023-10-25 PS2 documentation
2023-10-25 Cleanup code
2023-10-25 Fix readme
2023-10-25 Setup instructions
2023-10-25 Add breadboard photo
2023-10-25 Video links
2023-11-08 New OSD and switch from ps2 to spi
2023-11-08 Started custom misterynano firmware
2023-11-08 Link to u8g2
2023-11-08 Exclude build directories
2023-11-08 firmware readme
2023-11-08 Remove unused files
2023-11-21 Move file system handling into firmware
2023-11-21 Move file system handling out of core
2023-11-21 Update floppy simulation
2023-11-21 SPI protocol description
2023-11-21 Fix wiring
2023-11-24 Add ini files
2023-11-24 Installtion info
2023-11-28 Several floppy and OSD improvements
2023-11-30 Update SPI info
2023-11-30 Update SPI system and prepare flasher integration
2023-11-30 SPI protocol updates
2023-11-30 MiSTeryNano update modes
2023-11-30 Update mode info
2023-12-02 Update flash mode desciption
2023-12-04 Update joystick message
2023-12-05 Update firmware for joystick support etc
2023-12-05 HID joystick support
2023-12-06 Joystick limit fix
2023-12-15 SPI doc updated
2023-12-16 Aktualisieren von SPI.md
2023-12-16 Fix SD card IO doc
2023-12-17 Removed unused file
2023-12-18 Firmware interrupt support etc
2023-12-18 Include gowin config file
2023-12-18 Update docs to reflext the new IRQ line
2023-12-18 Core update
2023-12-18 Re-enable JTAG
2023-12-18 Add/update SD card related testbenchs
2023-12-18 Fix SDL menu test
2023-12-18 Aktualisieren von README.md
2023-12-19 Scrolling of long file names and paging
2023-12-19 Move installation instructions to a seperate file
2024-01-03 Update core
2024-01-03 Update firmware
2024-01-03 Update hdmi
2024-01-09 Add ACSI support
2024-01-10 Firmware compile with recent stock bouffalo sdk. Revert to older cherryusb
2024-01-14 Update video links
2024-01-14 Add cubase dongle support
2024-01-14 Major menu updates, finalized ACSI handling
2024-01-14 Add missing dependency
2024-01-15 HDD LEDs
2024-01-15 Update wiring diagram
2024-01-15 Update doc for latest release
2024-01-16 Add 20k flasher binary
2024-01-16 Add friend 20k explanation
2024-01-17 Enable exfat
2024-01-17 Windows instructions
2024-01-18 Start cbm inclusion
2024-01-18 Update db9 handling
2024-01-19 MiSTeryNano carrier board
2024-01-19 Keypad joystick support for c64
2024-01-19 Change joystick id
2024-01-21 Switch to Submodule for u8g2 lib
2024-01-23 Link to updated SDK
2024-01-23 Support for Atari and Amiga DB9 mice
2024-01-23 Prepare for xbox controller support
2024-01-23 Describe secondary TOS slot
2024-01-24 XBox controller support
2024-01-24 Second TOS ROM slot
2024-01-25 Windows doc updates
2024-01-25 Allow multiple file extensions to be searched for
2024-01-25 Update c64 menu and differentiate between usb joysticks
2024-01-26 Simplify toplevel to allow alternate setups
2024-01-26 Move MCU multiplexor into toplevel
2024-01-26 Update screenshot to avoid confusion
2024-01-26 Fix other confusing screenshot as well
2024-01-26 Adjust preferred STE TOS
2024-01-27 osd enhancement
2024-01-29 Build variant for RGBLCD equipped TN20k
2024-01-29 Enable internal BL616 for LCD variant
2024-01-29 c64 osd initial
2024-01-29 Make special reset behaviour core specific
2024-01-30 Update readmes
2024-01-31 c1541 reset for dos sel
2024-02-01 Expose printer port and fix #24
2024-02-02 Ignore A1 on second ACSI byte. Fixes #19
2024-02-02 Fix M0S compile
2024-02-05 Fix ACSI A1 handling
2024-02-08 FPGA cold boot detection
2024-02-08 Update SPI command description
2024-02-08 JLCPCB rendering
2024-02-08 TOS links
2024-02-08 add sid ain and midi
2024-02-08 fixed
2024-02-10 Pause to OSD
2024-02-11 c64 hid enhance
2024-02-13 M0S/M0S debugger
2024-02-13 Update images
2024-02-13 c64 osd cleanup
2024-02-14 Add encryted tang nano firmware binaries
2024-02-19 Fix extension parsing
2024-02-20 Fix handling of long menu entries
2024-02-20 Repository reorga
2024-02-20 Build variants
2024-02-20 Add support for Tang Primer 25K
2024-02-20 Allow json config in repo
2024-02-20 Photo of C51
2024-02-21 Enable use of internal BL616 for RGB LCD variant
2024-02-21 Fix i2s audio
2024-02-22 Add M0S PMOD
2024-02-22 Fix Primer 25k
2024-02-22 Fix/remove broken buffer handling
2024-02-23 Doc for Tang Primer 25K
2024-02-23 Rename firmware directory
2024-02-23 Use more convenient hex notation
2024-02-23 Fix addresses
2024-02-23 c64 core reset if pll changes
2024-02-23 Add Tang Mega 138k build variant
2024-02-24 Mention TM138k
2024-02-24 rescale image
2024-02-24 SVG source for wire diagram
2024-02-24 Readme for Tang Mega 138K
2024-02-24 Dualshock support for Mega 138k
2024-02-25 Update to local copy
2024-02-26 Reduce clock slightly for better hirez VGA compatibility
2024-02-26 Add troubleshooting guide
2024-02-26 Typo fixing ...
2024-03-01 c64 crt loader
2024-03-07 Allow for internal BL616 console
2024-03-10 add vic20
2024-03-10 wip vic20
2024-03-12 vic20 additions
2024-03-13 vic20 osd fix
2024-03-13 Add vic20 features (#32)
2024-03-26 add prg loader
2024-04-08 Update installation instructions to fix issue #36
2024-04-08 Fix build for gw_ide 1.9.9.02
2024-04-10 Fix #37
2024-04-10 Shorten path
2024-04-11 Add m0s wiring schema
2024-04-16 enable kernal loader
2024-04-22 Adopt to cherryusb 1.2.0
2024-04-22 Add firmware readme
2024-04-23 Initial support for bluetooth LE peripherials
2024-04-23 vic cia config
2024-04-24 Fix #38
2024-04-24 Explain R9 BOM issue
2024-04-24 Add link to openfpgaloader help
2024-04-27 add mountpoints
2024-04-29 Test alternate way to determine position in cluster chain
2024-04-30 add mountpoints (#41)
2024-05-08 Re-add deleted vic-20 entries
2024-05-11 Initial Amiga support
2024-05-12 tape sid8580
2024-05-12 digifix default
2024-05-12 Adopt to increased drives
2024-05-15 tape sound add
2024-05-15 tape sound add (#47)
2024-05-17 Add pure M0S board variant
2024-05-17 Update production data
2024-05-17 update production info
2024-05-17 Adjust image path
2024-05-17 Typeo
2024-05-20 c64 core sid options
2024-05-24 Fix Amiga keymap
2024-05-24 Update Amiga defaukt floppy names
2024-05-24 C64 core sid options (#48)
2024-05-25 Add Amiga floppy entries
2024-05-29 Extend Amiga OSD
2024-05-29 Amiga Right Alt fix
2024-06-01 Update NanoMig menu
2024-06-01 Fix amiga menu
2024-06-01 Fix nanomig video settings
2024-06-07 3D Housing
2024-06-07 3D Housing photo
2024-06-09 dualsid
2024-06-09 c64 sid fc disabled
2024-06-13 swiftlink uart prepare
2024-06-13 C64 core swiftlink prepare (#54)
2024-06-15 Updated LCD variant to use external M0S
2024-06-16 c64 sid filter
2024-06-16 Revert "c64 sid filter"
    This reverts commit 77bb7b7ef93a7607b9cdf9d934054456abbcb784.
2024-06-17 c64 loadable filter
2024-06-19 Disable broken btble driver
2024-06-20 Bring joystick signals into hid clock domain
2024-06-21 c64core mountpoint flt filter
2024-06-21 c64core mountpoint flt filter (#56)
2024-06-25 c64 core fix support for 6 drives
2024-07-26 sdk update and c64 core keymap update
2024-07-27 vic20 keymap changed
2024-07-27 updated sdk support and c64 plus vic20 core keymap update (#60)
2024-09-01 Update LCD variant to use FPGA companion
2024-09-04 Bring IKBD and 200hz timer into 32 mhz clock domain
2024-09-04 Fix ikbd clock divider and update sysclk to support rs232
2024-09-06 Small hid and mfp adjustments finally fixing #61
2024-09-06 Refer to FPGA Companion
2024-10-09 HDMI version with Companion on pins like LCD version
2024-10-09 Naming fixed
2024-10-18 C64 and VIC20 OSD update
2024-10-18 C64 and VIC20 OSD update (#65)
2024-10-19 a2600_c64_extrabtn
2024-10-19 a2600_c64_extrabtn (#66)
2024-10-20 c64 core crt unload add
2024-10-20 c64 core crt unload add (#67)
2024-10-29 Add full Atari ST simulation
2024-10-30 Add hdmenu image creator
2024-11-27 Initial release of mini keyboard
2024-11-27 Fix filename typo
2024-12-01 All US keycaps done
2024-12-02 Update keycap exporter
2024-12-03 Fixing some key caps for print
2024-12-03 Add fkey alignment grid
2024-12-12 Keycaps label adjustments to allow printing
2024-12-16 Keyboard working
2024-12-16 Update 3d paths
2024-12-17 Implement caps lock led
2024-12-22 Add new video
2024-12-22 Fix dropdown
2024-12-22 Fix video link
2025-01-12 Keyboard assembly fotos
2025-01-12 Remove duplicate image
2025-01-12 Fix image url
2025-01-12 link to video
2025-03-20 Update MFP to stream nicely over WiFi
2025-03-21 Fix built-in XML config
2025-03-24 Update included config
2025-03-24 Include config hex
2025-03-25 Switch to generic core implementation
2025-03-25 Move SPI doc to FPGA Companion
2025-03-26 Support for Tang Console 60k
2025-03-27 Add missing config files
2025-03-27 Update project files
2025-03-27 Further build file fix
2025-03-27 Fix link
2025-03-27 Link to external hardware
2025-03-27 Adjust dualshock PMOD pin mapping
2025-03-27 DS2 PMOD desciption
2025-03-28 Update doc
2025-04-17 Video link to T20 demo
2025-04-18 Add beta support for Efinix Trion T20BGA256
2025-04-18 Add photo
2025-04-19 Add spherical image
2025-04-25 Link to BBS video
2025-04-26 Add missing config xml
2025-04-30 Trigger system interrupt on FPGA button event
2025-05-06 T20BGA256 addon board
2025-05-19 Add M0S support version of Misteryshield20k case base and the OpenSCAD files for the case, update its README
2025-05-22 Add misteryshield lite
2025-05-22 Resize images
2025-05-23 Add photo of modified pcb
2025-05-24 Add copyleft info and comments to ms20k case SCAD source files
2025-06-18 A simple housing for the MiSTeryNano Lite
2025-07-19 onboard BL616
2025-07-19 onboard BL616 (#83)
2025-07-20 tc60k bl616 support
2025-07-20 tc60k bl616 support (#86)
2025-07-21 bl616 build fix
2025-07-21 tc60k led
2025-07-22 Bl616 build definition (#88)
